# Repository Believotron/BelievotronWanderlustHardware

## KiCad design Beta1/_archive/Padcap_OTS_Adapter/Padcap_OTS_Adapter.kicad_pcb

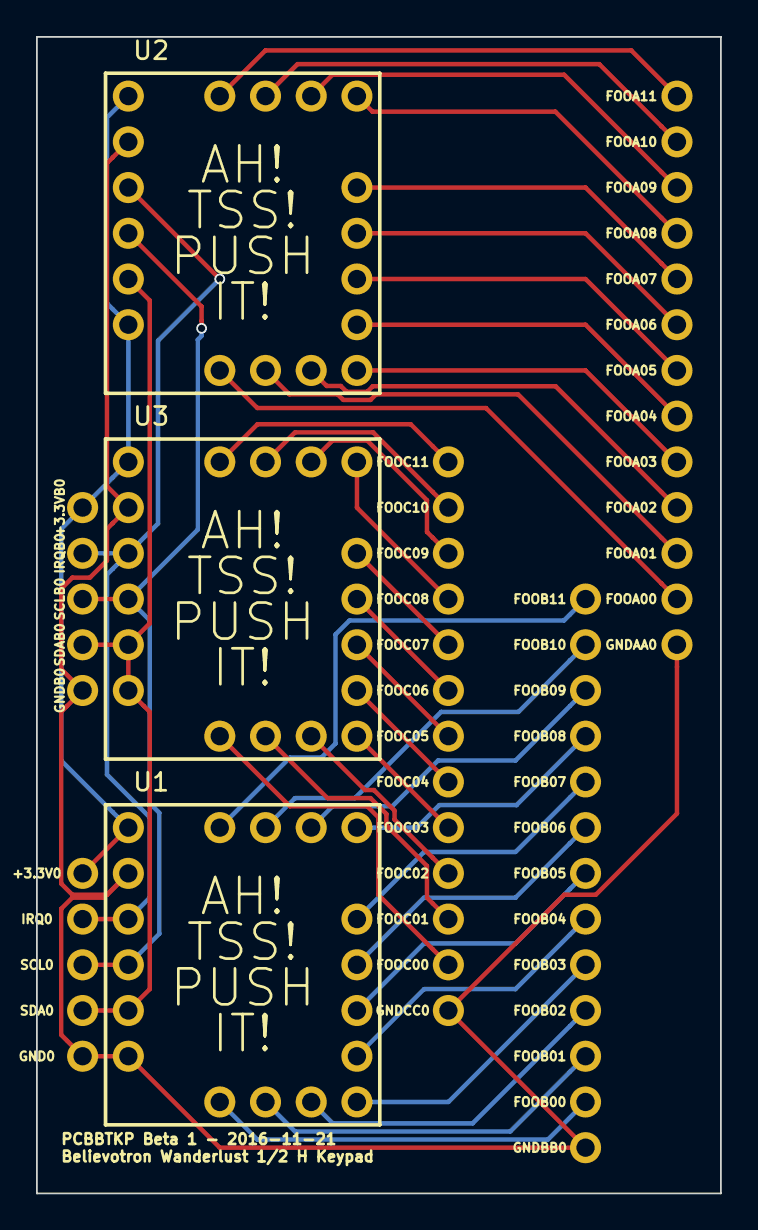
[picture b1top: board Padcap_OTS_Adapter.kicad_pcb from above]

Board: 2 copper layers, 38.0 x 64.2 mm, 52 parts (0 on the bottom side), 41 nets.

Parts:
+3.3V0, +3.3VB0: CONN_01X01; single_0.1
FOOA00, FOOA01, FOOA02, FOOA03, FOOA04, FOOA05, FOOA06, FOOA07, FOOA08, FOOA09, FOOA10, FOOA11: CONN_01X01; single_0.1
FOOB00, FOOB01, FOOB02, FOOB03, FOOB04, FOOB05, FOOB06, FOOB07, FOOB08, FOOB09, FOOB10, FOOB11: CONN_01X01; single_0.1
FOOC00, FOOC01, FOOC02, FOOC03, FOOC04, FOOC05, FOOC06, FOOC07, FOOC08, FOOC09, FOOC10, FOOC11: CONN_01X01; single_0.1
GND0: CONN_01X01; single_0.1
GNDAA0: CONN_01X01; single_0.1
GNDB0: CONN_01X01; single_0.1
GNDBB0: CONN_01X01; single_0.1
GNDCC0: CONN_01X01; single_0.1
IRQ0: CONN_01X01; single_0.1
IRQB0: CONN_01X01; single_0.1
SCL0: CONN_01X01; single_0.1
SCLB0: CONN_01X01; single_0.1
SDA0: CONN_01X01; single_0.1
SDAB0: CONN_01X01; single_0.1
U1, U2, U3: MPR121TH

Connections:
+3V3: +3.3V0.1, +3.3VB0.1, U1.+3.3, U2.+3.3, U2.ADDR, U3.+3.3
/IRQ: IRQ0.1, IRQB0.1, U1.IRQ, U2.IRQ, U3.IRQ
/SCL: SCL0.1, SCLB0.1, U1.SCL, U2.SCL, U3.SCL
/SDA: SDA0.1, SDAB0.1, U1.SDA, U2.SDA, U3.ADDR, U3.SDA
GND: GND0.1, GNDAA0.1, GNDB0.1, GNDBB0.1, GNDCC0.1, U1.ADDR, U1.GND, U2.GND, U3.GND
unnamed: FOOA00.1, U2.P00
unnamed: FOOA01.1, U2.P01
unnamed: FOOA02.1, U2.P02
unnamed: FOOA03.1, U2.P03
unnamed: FOOA04.1, U2.P04
unnamed: FOOA05.1, U2.P05
unnamed: FOOA06.1, U2.P06
unnamed: FOOA07.1, U2.P07
unnamed: FOOA08.1, U2.P08
unnamed: FOOA09.1, U2.P09
unnamed: FOOA10.1, U2.P10
unnamed: FOOA11.1, U2.P11
unnamed: FOOB00.1, U1.P00
unnamed: FOOB01.1, U1.P01
unnamed: FOOB02.1, U1.P02
unnamed: FOOB03.1, U1.P03
unnamed: FOOB04.1, U1.P04
unnamed: FOOB05.1, U1.P05
unnamed: FOOB06.1, U1.P06
unnamed: FOOB07.1, U1.P07
unnamed: FOOB08.1, U1.P08
unnamed: FOOB09.1, U1.P09
unnamed: FOOB10.1, U1.P10
unnamed: FOOB11.1, U1.P11
unnamed: FOOC00.1, U3.P00
unnamed: FOOC01.1, U3.P01
unnamed: FOOC02.1, U3.P02
unnamed: FOOC03.1, U3.P03
unnamed: FOOC04.1, U3.P04
unnamed: FOOC05.1, U3.P05
unnamed: FOOC06.1, U3.P06
unnamed: FOOC07.1, U3.P07
unnamed: FOOC08.1, U3.P08
unnamed: FOOC09.1, U3.P09
unnamed: FOOC10.1, U3.P10
unnamed: FOOC11.1, U3.P11
